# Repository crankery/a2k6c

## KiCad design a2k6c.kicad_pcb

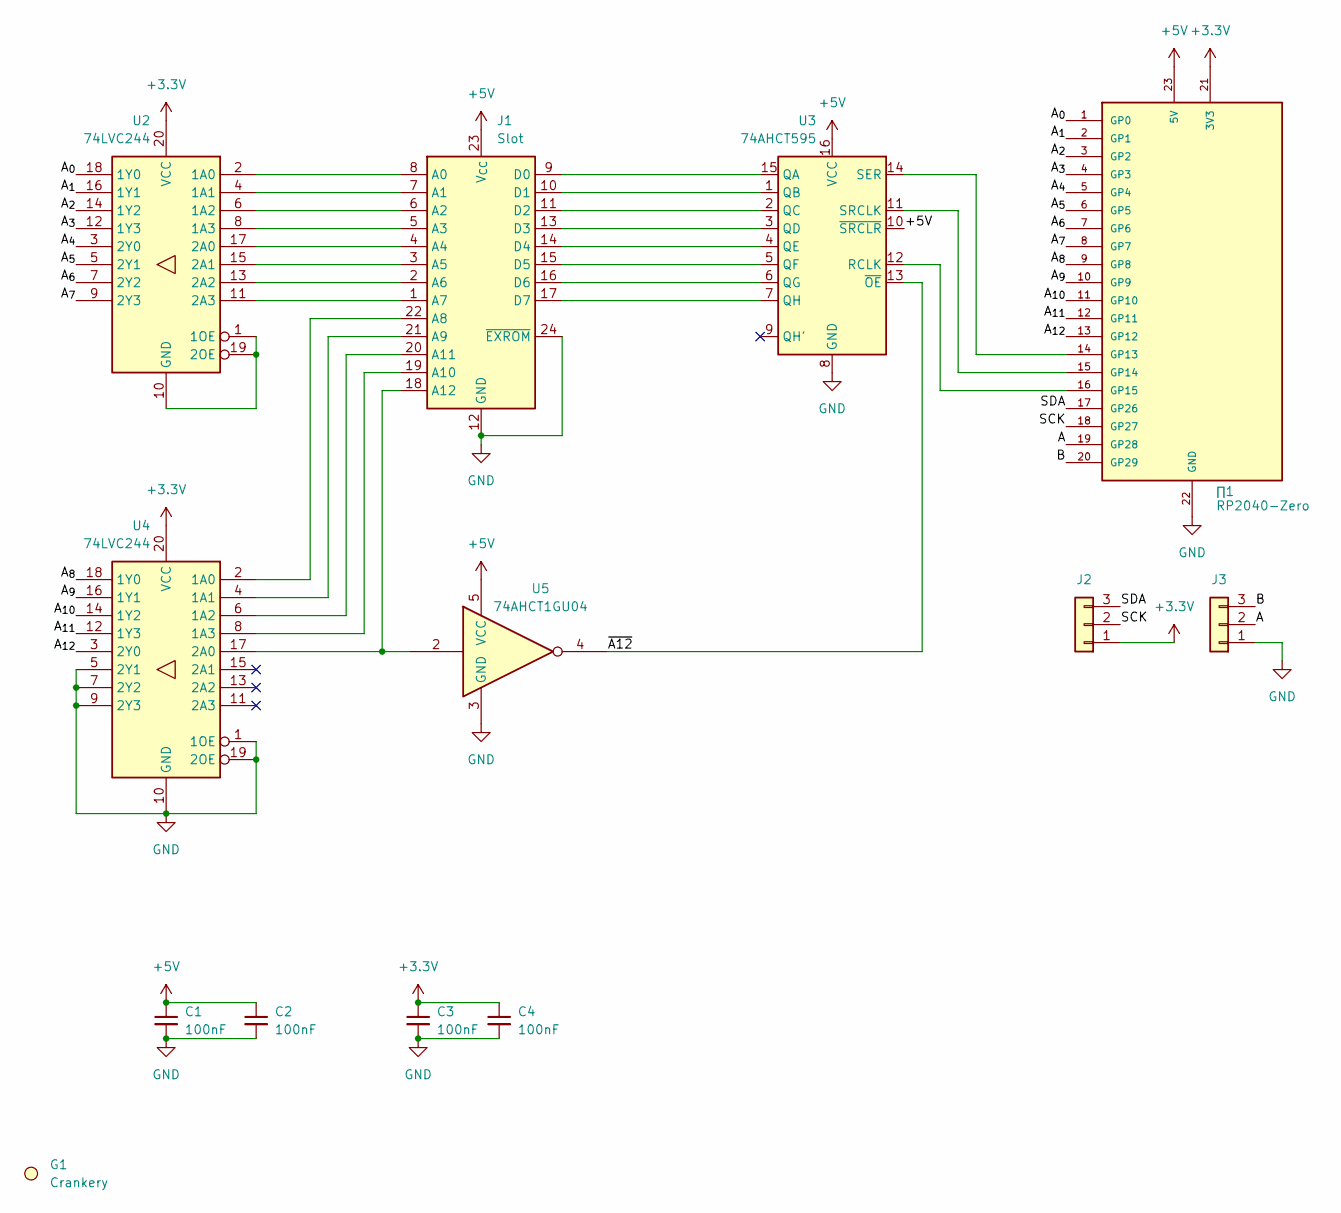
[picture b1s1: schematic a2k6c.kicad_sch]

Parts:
C1, C2, C3, C4: 100nF; C_1206_3216Metric_Pad1.33x1.80mm_HandSolder
G1: Crankery; crankery_small
J1: Slot; ATARI_VCS_CARD_EDGE
J2: I^{2}C; SolderWire-0.1sqmm_1x03_P3.6mm_D0.4mm_OD1mm
J3: Buttons; SolderWire-0.1sqmm_1x03_P3.6mm_D0.4mm_OD1mm
U2, U4: 74LVC244; SOIC-20W_7.5x12.8mm_P1.27mm
U3: 74AHCT595; SOIC-16_3.9x9.9mm_P1.27mm
U5: 74AHCT1GU04; SOT-23-5_HandSoldering
∏1: RP2040-Zero; MODULE_RP2040-ZERO_Basic

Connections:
+3.3V: C3.1, C4.1, J2.1, U2.20 (VCC), U4.20 (VCC), ∏1.21 (3V3)
+5V: C1.1, C2.1, J1.23 (V_{CC}), U3.10 (~SRCLR), U3.16 (VCC), U5.5 (VCC), ∏1.23 (5V)
/A: J3.2, ∏1.19 (GP28)
/A_{0}: U2.18 (1Y0), ∏1.1 (GP0)
/A_{1}: U2.16 (1Y1), ∏1.2 (GP1)
/A_{2}: U2.14 (1Y2), ∏1.3 (GP2)
/A_{3}: U2.12 (1Y3), ∏1.4 (GP3)
/A_{4}: U2.3 (2Y0), ∏1.5 (GP4)
/A_{5}: U2.5 (2Y1), ∏1.6 (GP5)
/A_{6}: U2.7 (2Y2), ∏1.7 (GP6)
/A_{7}: U2.9 (2Y3), ∏1.8 (GP7)
/A_{8}: U4.18 (1Y0), ∏1.9 (GP8)
/A_{9}: U4.16 (1Y1), ∏1.10 (GP9)
/A_{10}: U4.14 (1Y2), ∏1.11 (GP10)
/A_{11}: U4.12 (1Y3), ∏1.12 (GP11)
/A_{12}: U4.3 (2Y0), ∏1.13 (GP12)
/B: J3.3, ∏1.20 (GP29)
/SCK: J2.2, ∏1.18 (GP27)
/SDA: J2.3, ∏1.17 (GP26)
/~A12: U3.13 (~OE), U5.4
GND: C1.2, C2.2, C3.2, C4.2, J1.12 (GND), J1.24 (~EXROM), J3.1, U3.8 (GND), U4.1 (1OE), U4.5 (2Y1), U4.7 (2Y2), U4.9 (2Y3), U4.10 (GND), U4.19 (2OE), U5.3 (GND), ∏1.22 (GND)
unnamed: J1.8 (A0), U2.2 (1A0)
unnamed: J1.7 (A1), U2.4 (1A1)
unnamed: J1.6 (A2), U2.6 (1A2)
unnamed: J1.5 (A3), U2.8 (1A3)
unnamed: J1.4 (A4), U2.17 (2A0)
unnamed: J1.3 (A5), U2.15 (2A1)
unnamed: J1.2 (A6), U2.13 (2A2)
unnamed: J1.1 (A7), U2.11 (2A3)
unnamed: J1.22 (A8), U4.2 (1A0)
unnamed: J1.21 (A9), U4.4 (1A1)
unnamed: J1.19 (A10), U4.8 (1A3)
unnamed: J1.20 (A11), U4.6 (1A2)
unnamed: J1.18 (A12), U4.17 (2A0), U5.2
unnamed: J1.9 (D0), U3.15 (QA)
unnamed: J1.10 (D1), U3.1 (QB)
unnamed: J1.11 (D2), U3.2 (QC)
unnamed: J1.13 (D3), U3.3 (QD)
unnamed: J1.14 (D4), U3.4 (QE)
unnamed: J1.15 (D5), U3.5 (QF)
unnamed: J1.16 (D6), U3.6 (QG)
unnamed: J1.17 (D7), U3.7 (QH)
unnamed: U2.1 (1OE), U2.10 (GND), U2.19 (2OE)
unnamed: U3.12 (RCLK), ∏1.16 (GP15)
unnamed: U3.14 (SER), ∏1.14 (GP13)
unnamed: U3.11 (SRCLK), ∏1.15 (GP14)

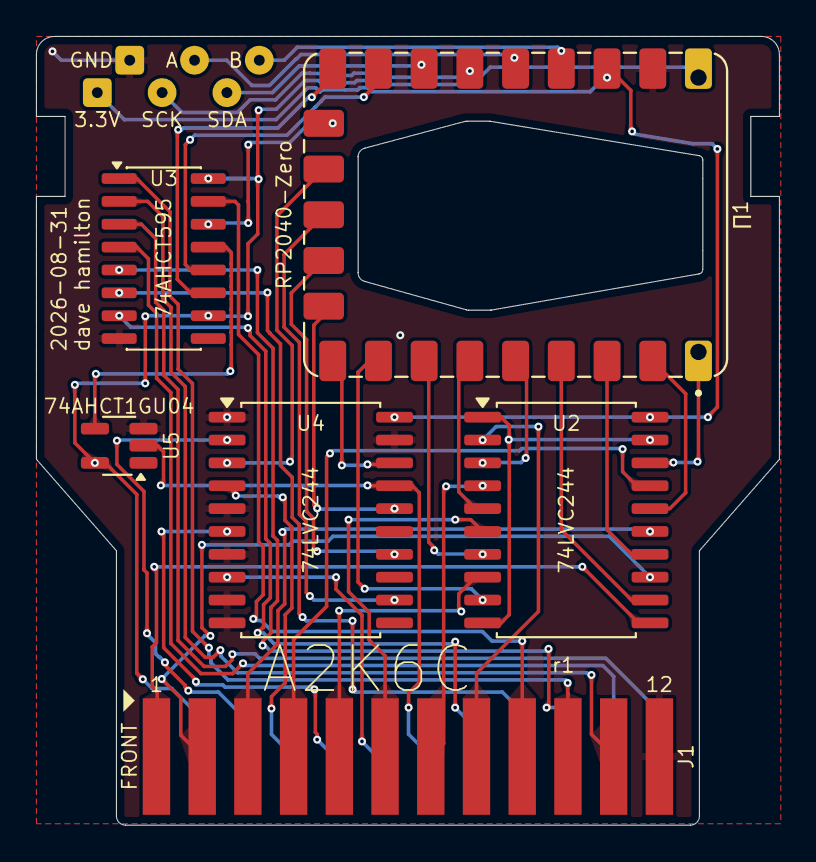
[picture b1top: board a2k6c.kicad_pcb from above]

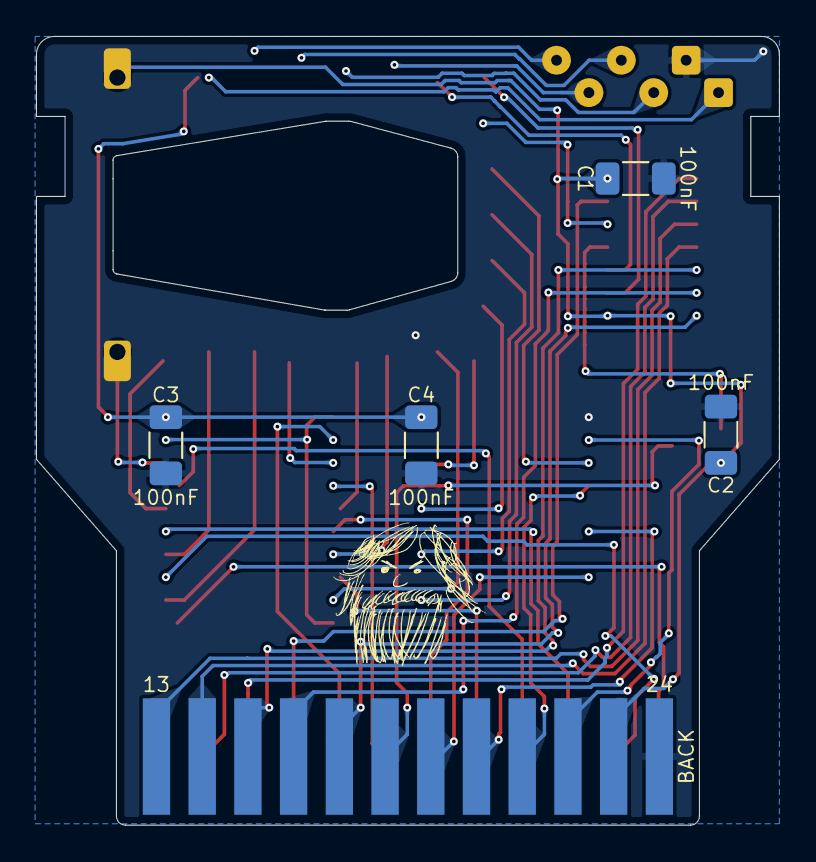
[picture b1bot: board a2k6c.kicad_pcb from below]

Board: 2 copper layers, 41.3 x 43.8 mm, 13 parts (6 on the bottom side), 46 nets.
